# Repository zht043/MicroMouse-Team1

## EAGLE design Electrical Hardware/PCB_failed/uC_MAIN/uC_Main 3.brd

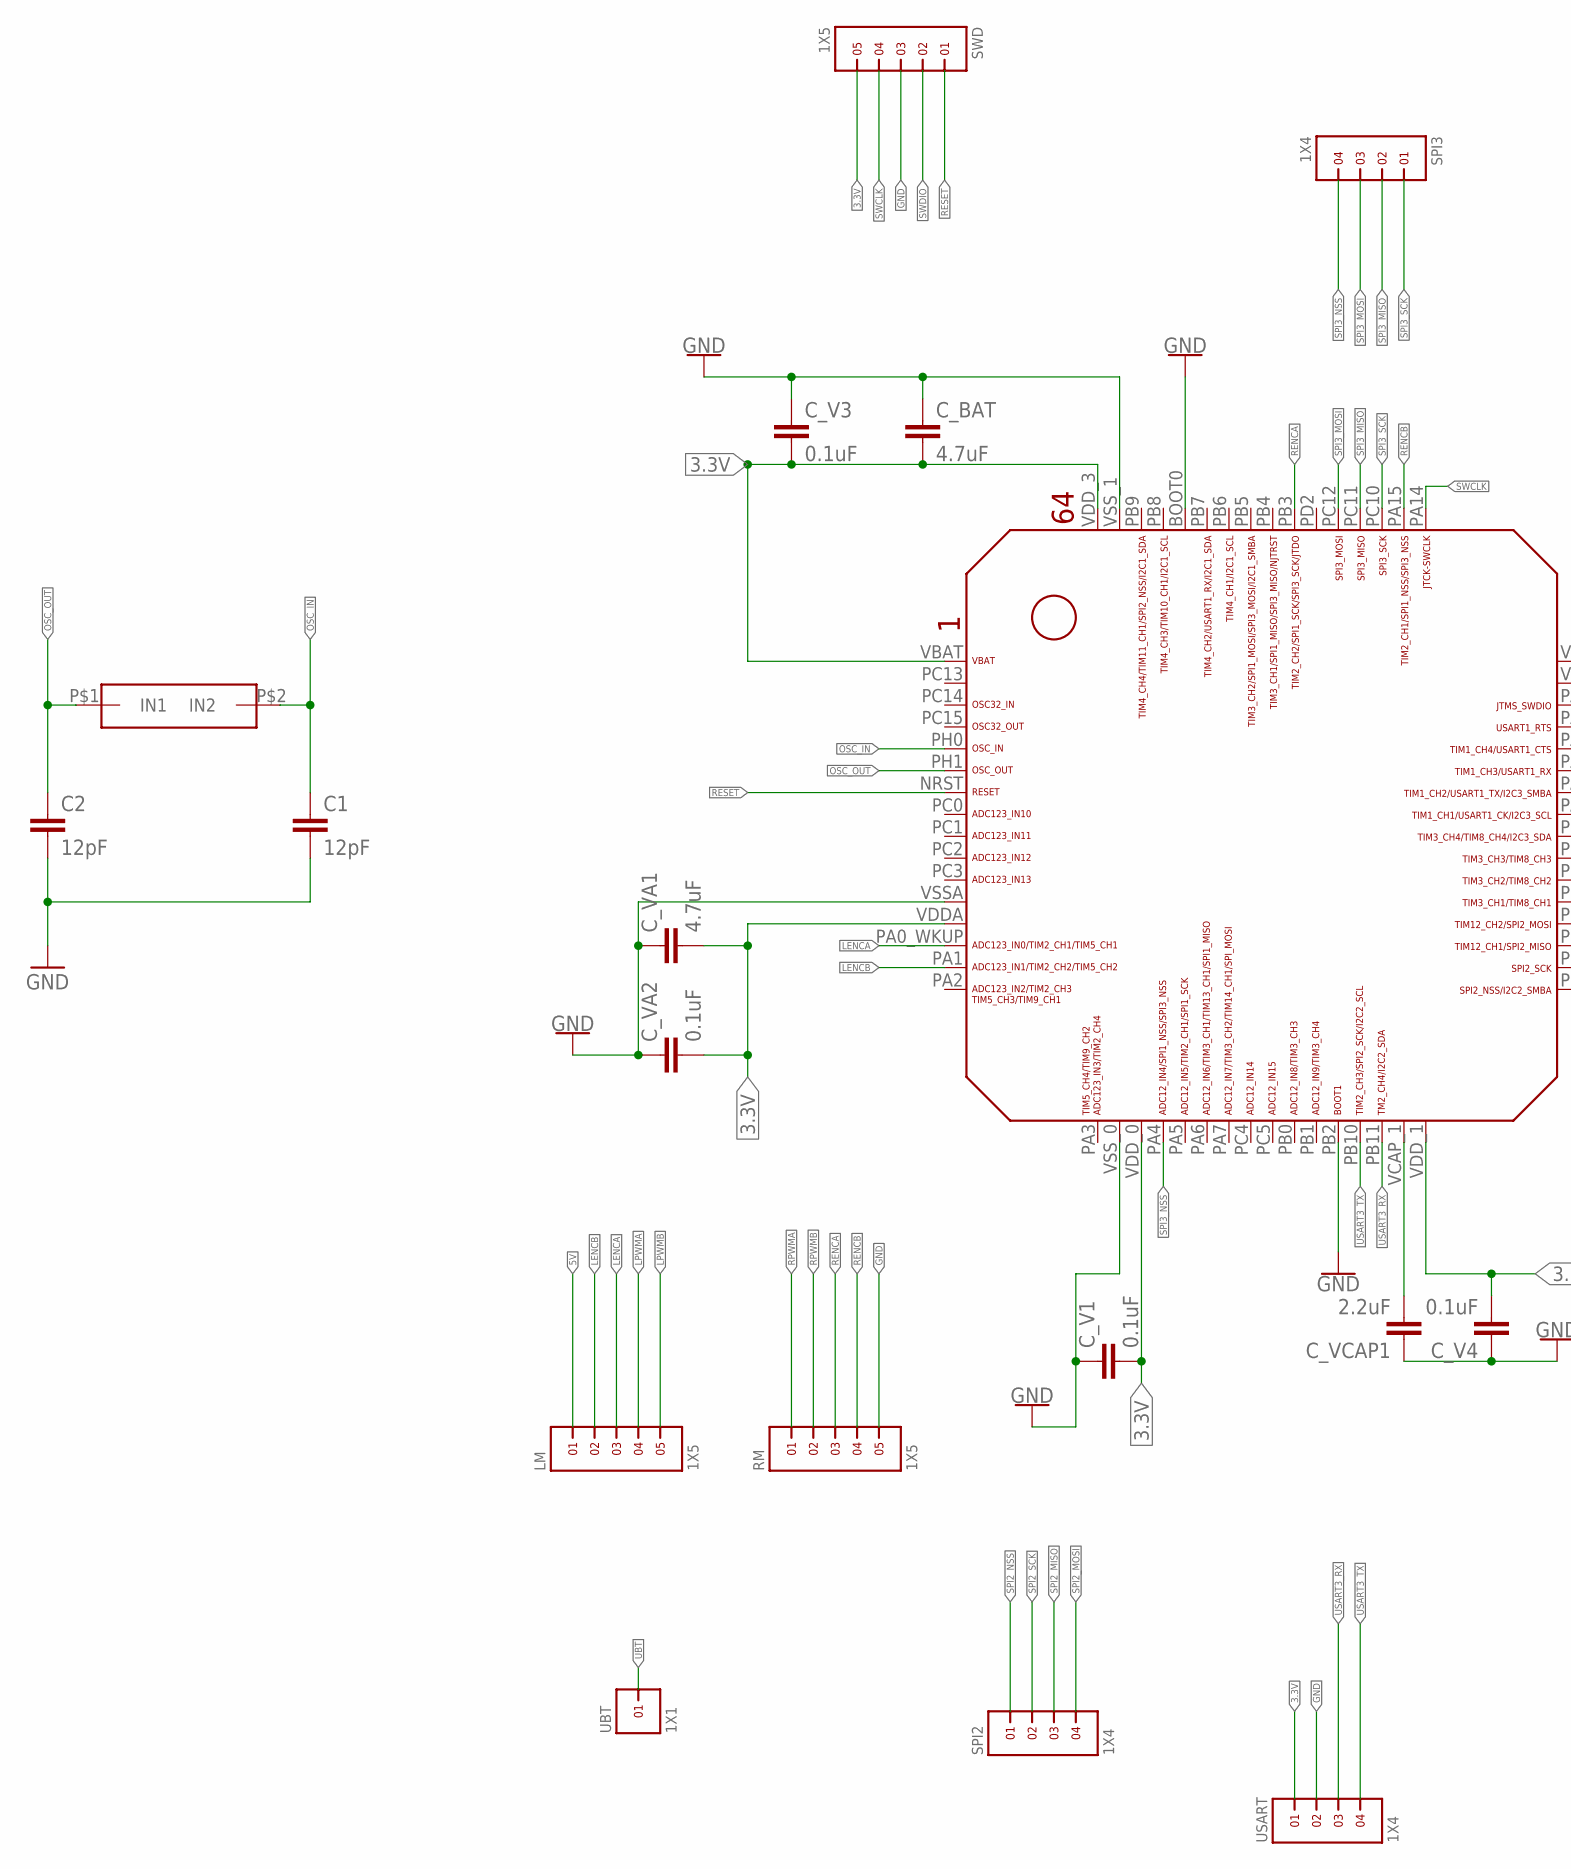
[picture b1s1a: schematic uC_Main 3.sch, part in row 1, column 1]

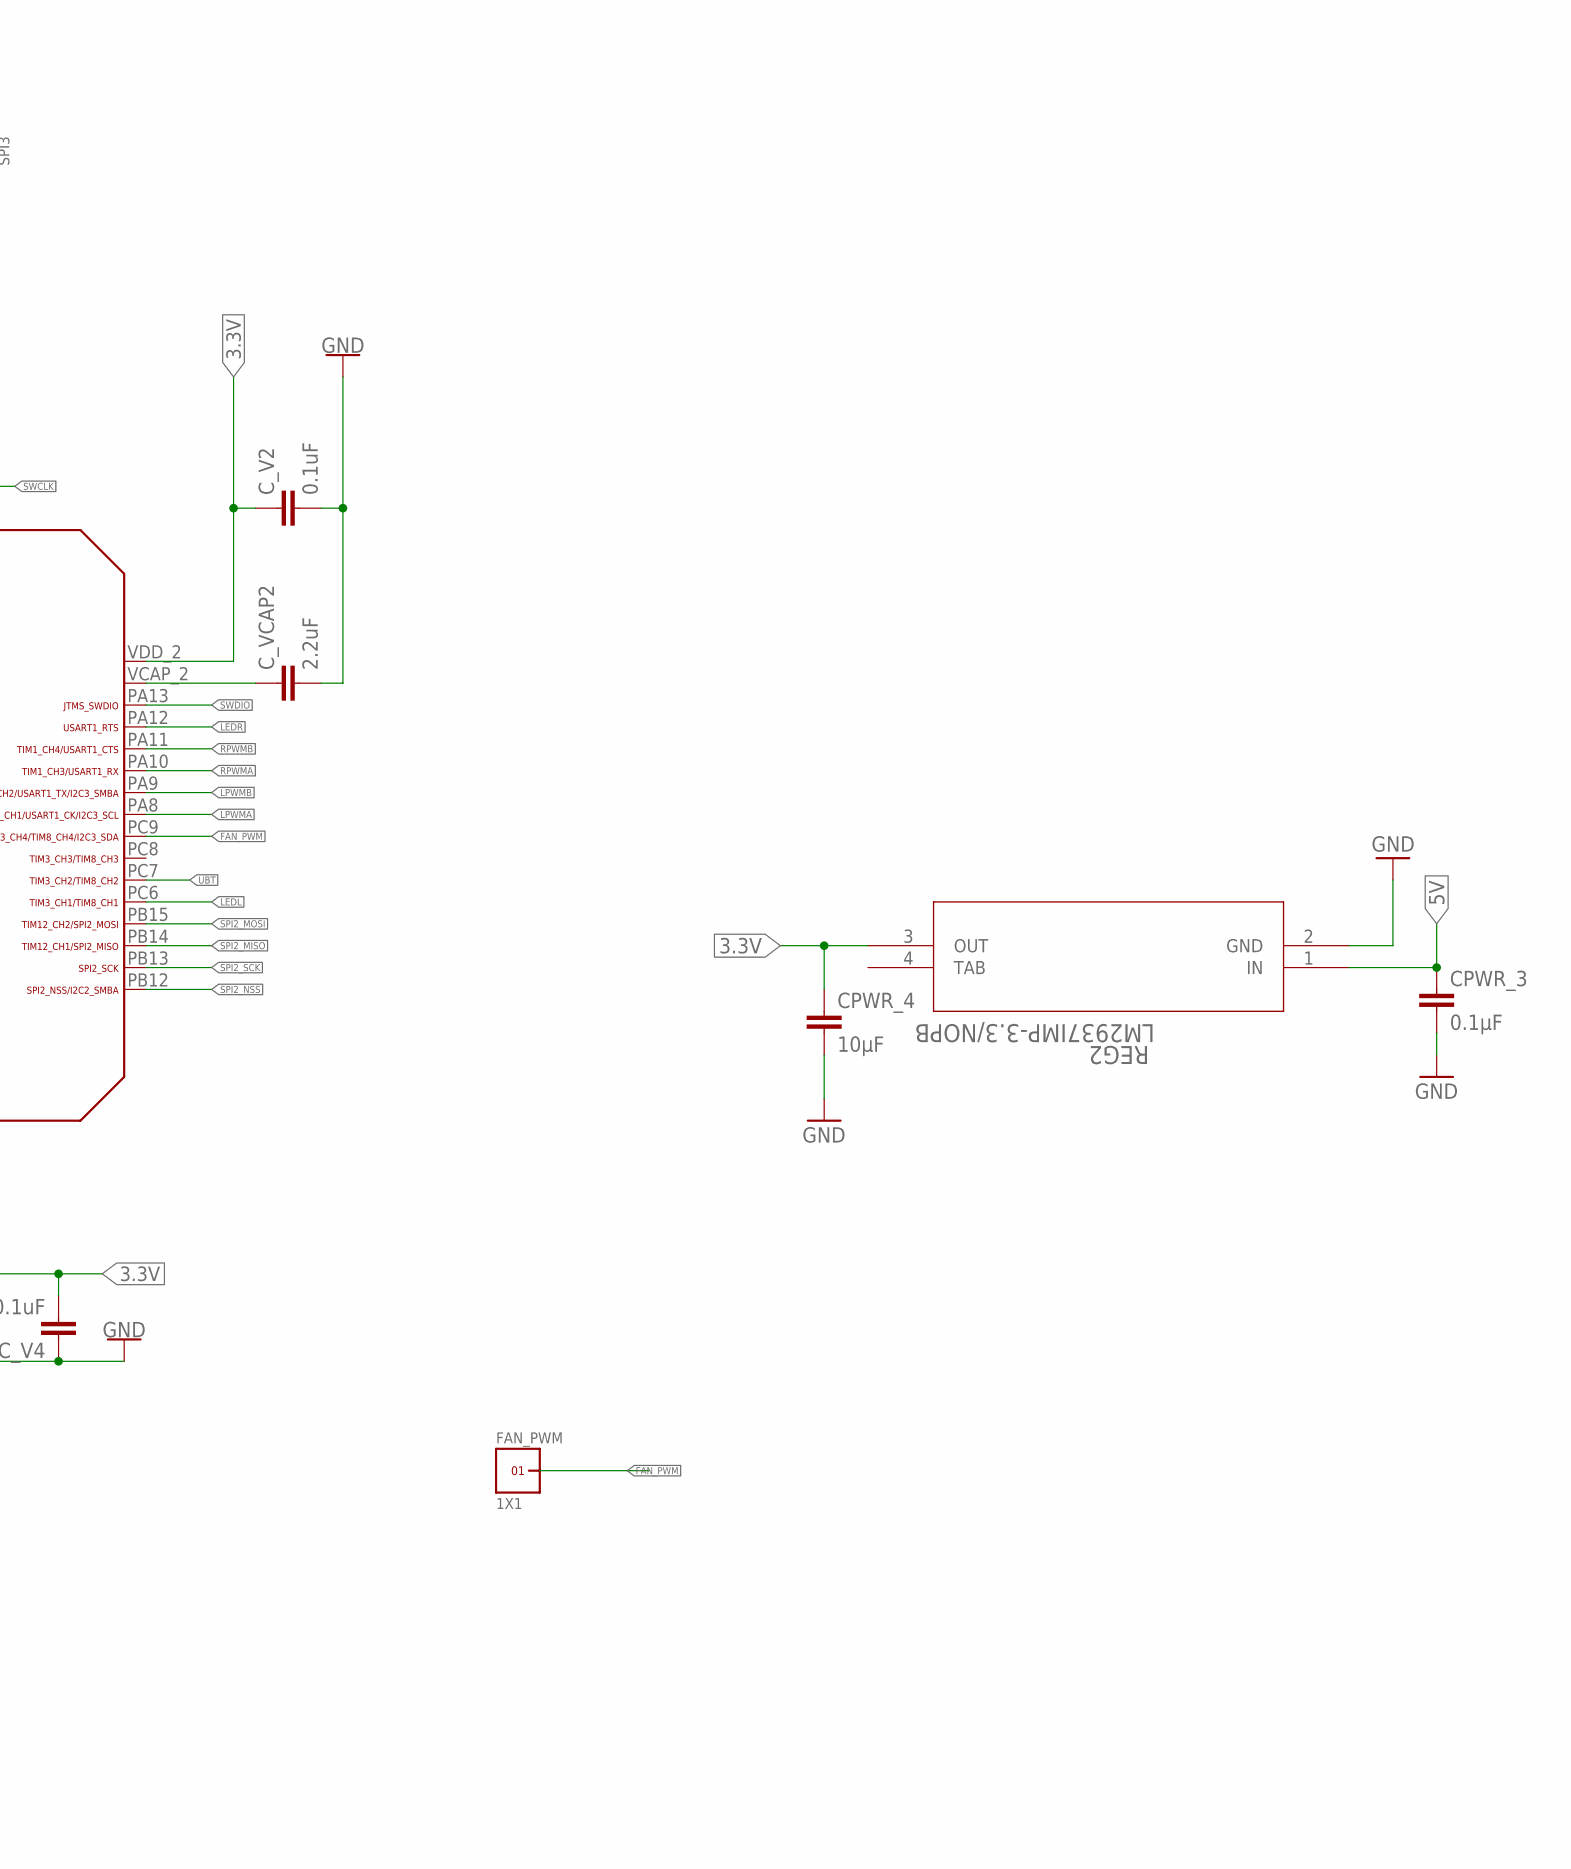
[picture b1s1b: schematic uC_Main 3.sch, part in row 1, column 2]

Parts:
C1, C2: 12pF; 0603
CPWR_3: 0.1µF; 0805
CPWR_4: 10µF; 0805
C_BAT: 4.7uF; 0805@1
C_V1, C_V2, C_V3, C_V4: 0.1uF; 0805@1
C_VA1: 4.7uF; 0805@1
C_VA2: 0.1uF; 0805@1
C_VCAP1, C_VCAP2: 2.2uF; 0805@1
FAN_PWM: 1X1
LM: 1X5
REG2: LM2937IMP-3.3/NOPB; MP04A
RM: 1X5
SPI2, SPI3: 1X4
SWD: 1X5
U$1: STM32F405/415_LQFP64
U$2: OSC
UBT: 1X1
USART: 1X4

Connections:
3.3V: CPWR_4.1, C_BAT.2, C_V1.2, C_V2.1, C_V3.2, C_V4.2, C_VA1.2, C_VA2.2, REG2.3 (OUT), SWD.5, U$1.VBAT, U$1.VDDA, U$1.VDD_0, U$1.VDD_1, U$1.VDD_2, U$1.VDD_3, USART.1
5V: CPWR_3.1, LM.1, REG2.1 (IN)
FAN_PWM: FAN_PWM.1, U$1.PC9
GND: C1.2, C2.2, CPWR_3.2, CPWR_4.2, C_BAT.1, C_V1.1, C_V2.2, C_V3.1, C_V4.1, C_VA1.1, C_VA2.1, C_VCAP1.1, C_VCAP2.2, REG2.2 (GND), RM.5, SWD.3, U$1.BOOT0, U$1.PB2, U$1.VSSA, U$1.VSS_0, U$1.VSS_1, USART.2
LEDL: U$1.PC6
LEDR: U$1.PA12
LENCA: LM.3, U$1.PA0_WKUP (PA0_AKUP)
LENCB: LM.2, U$1.PA1
LPWMA: LM.4, U$1.PA8
LPWMB: LM.5, U$1.PA9
OSC_IN: C1.1, U$1.PH0, U$2.P$2 (IN2)
OSC_OUT: C2.1, U$1.PH1, U$2.P$1 (IN1)
RENCA: RM.3, U$1.PB3
RENCB: RM.4, U$1.PA15
RESET: SWD.1, U$1.NRST
RPWMA: RM.1, U$1.PA10
RPWMB: RM.2, U$1.PA11
SPI2_MISO: SPI2.3, U$1.PB14
SPI2_MOSI: SPI2.4, U$1.PB15
SPI2_NSS: SPI2.1, U$1.PB12
SPI2_SCK: SPI2.2, U$1.PB13
SPI3_MISO: SPI3.2, U$1.PC11
SPI3_MOSI: SPI3.3, U$1.PC12
SPI3_NSS: SPI3.4, U$1.PA4
SPI3_SCK: SPI3.1, U$1.PC10
SWCLK: SWD.4, U$1.PA14
SWDIO: SWD.2, U$1.PA13
TAB: REG2.4 (TAB)
UBT: U$1.PC7, UBT.1
USART3_RX: U$1.PB11, USART.3
USART3_TX: U$1.PB10, USART.4
VCAP_1: C_VCAP1.2, U$1.VCAP_1
VCAP_2: C_VCAP2.1, U$1.VCAP_2

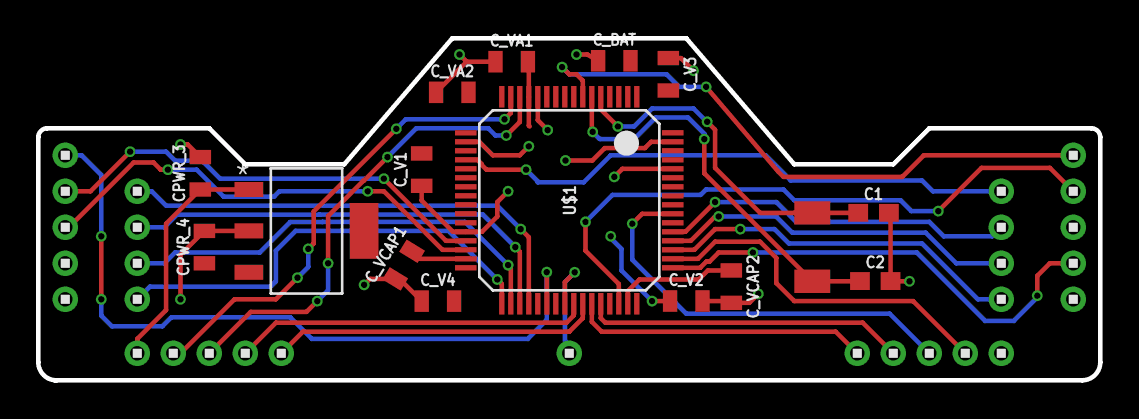
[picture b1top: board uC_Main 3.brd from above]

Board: 2 copper layers, 59.0 x 19.0 mm, 24 parts (0 on the bottom side), 30 nets.

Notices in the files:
parts and their libraries:
SparkFun-Capacitors: Licensing: Creative Commons ShareAlike 4.0 International - https://creativecommons.org/licenses/by-sa/4.0
COPYRIGHT: Copyright C 2015 Accelerated Designs. All rights reserved
